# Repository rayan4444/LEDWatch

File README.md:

# LEDWatch
LEDWatch: documentation coming soon

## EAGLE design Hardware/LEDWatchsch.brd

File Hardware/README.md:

# LED Watch Hardware

<!-- Schematic and explanations  -->
<!-- PCB file and explanations -->
<!-- Assembly instructions -->
<!-- Ordering: BOM and PCB, maybe Tindie store? -->

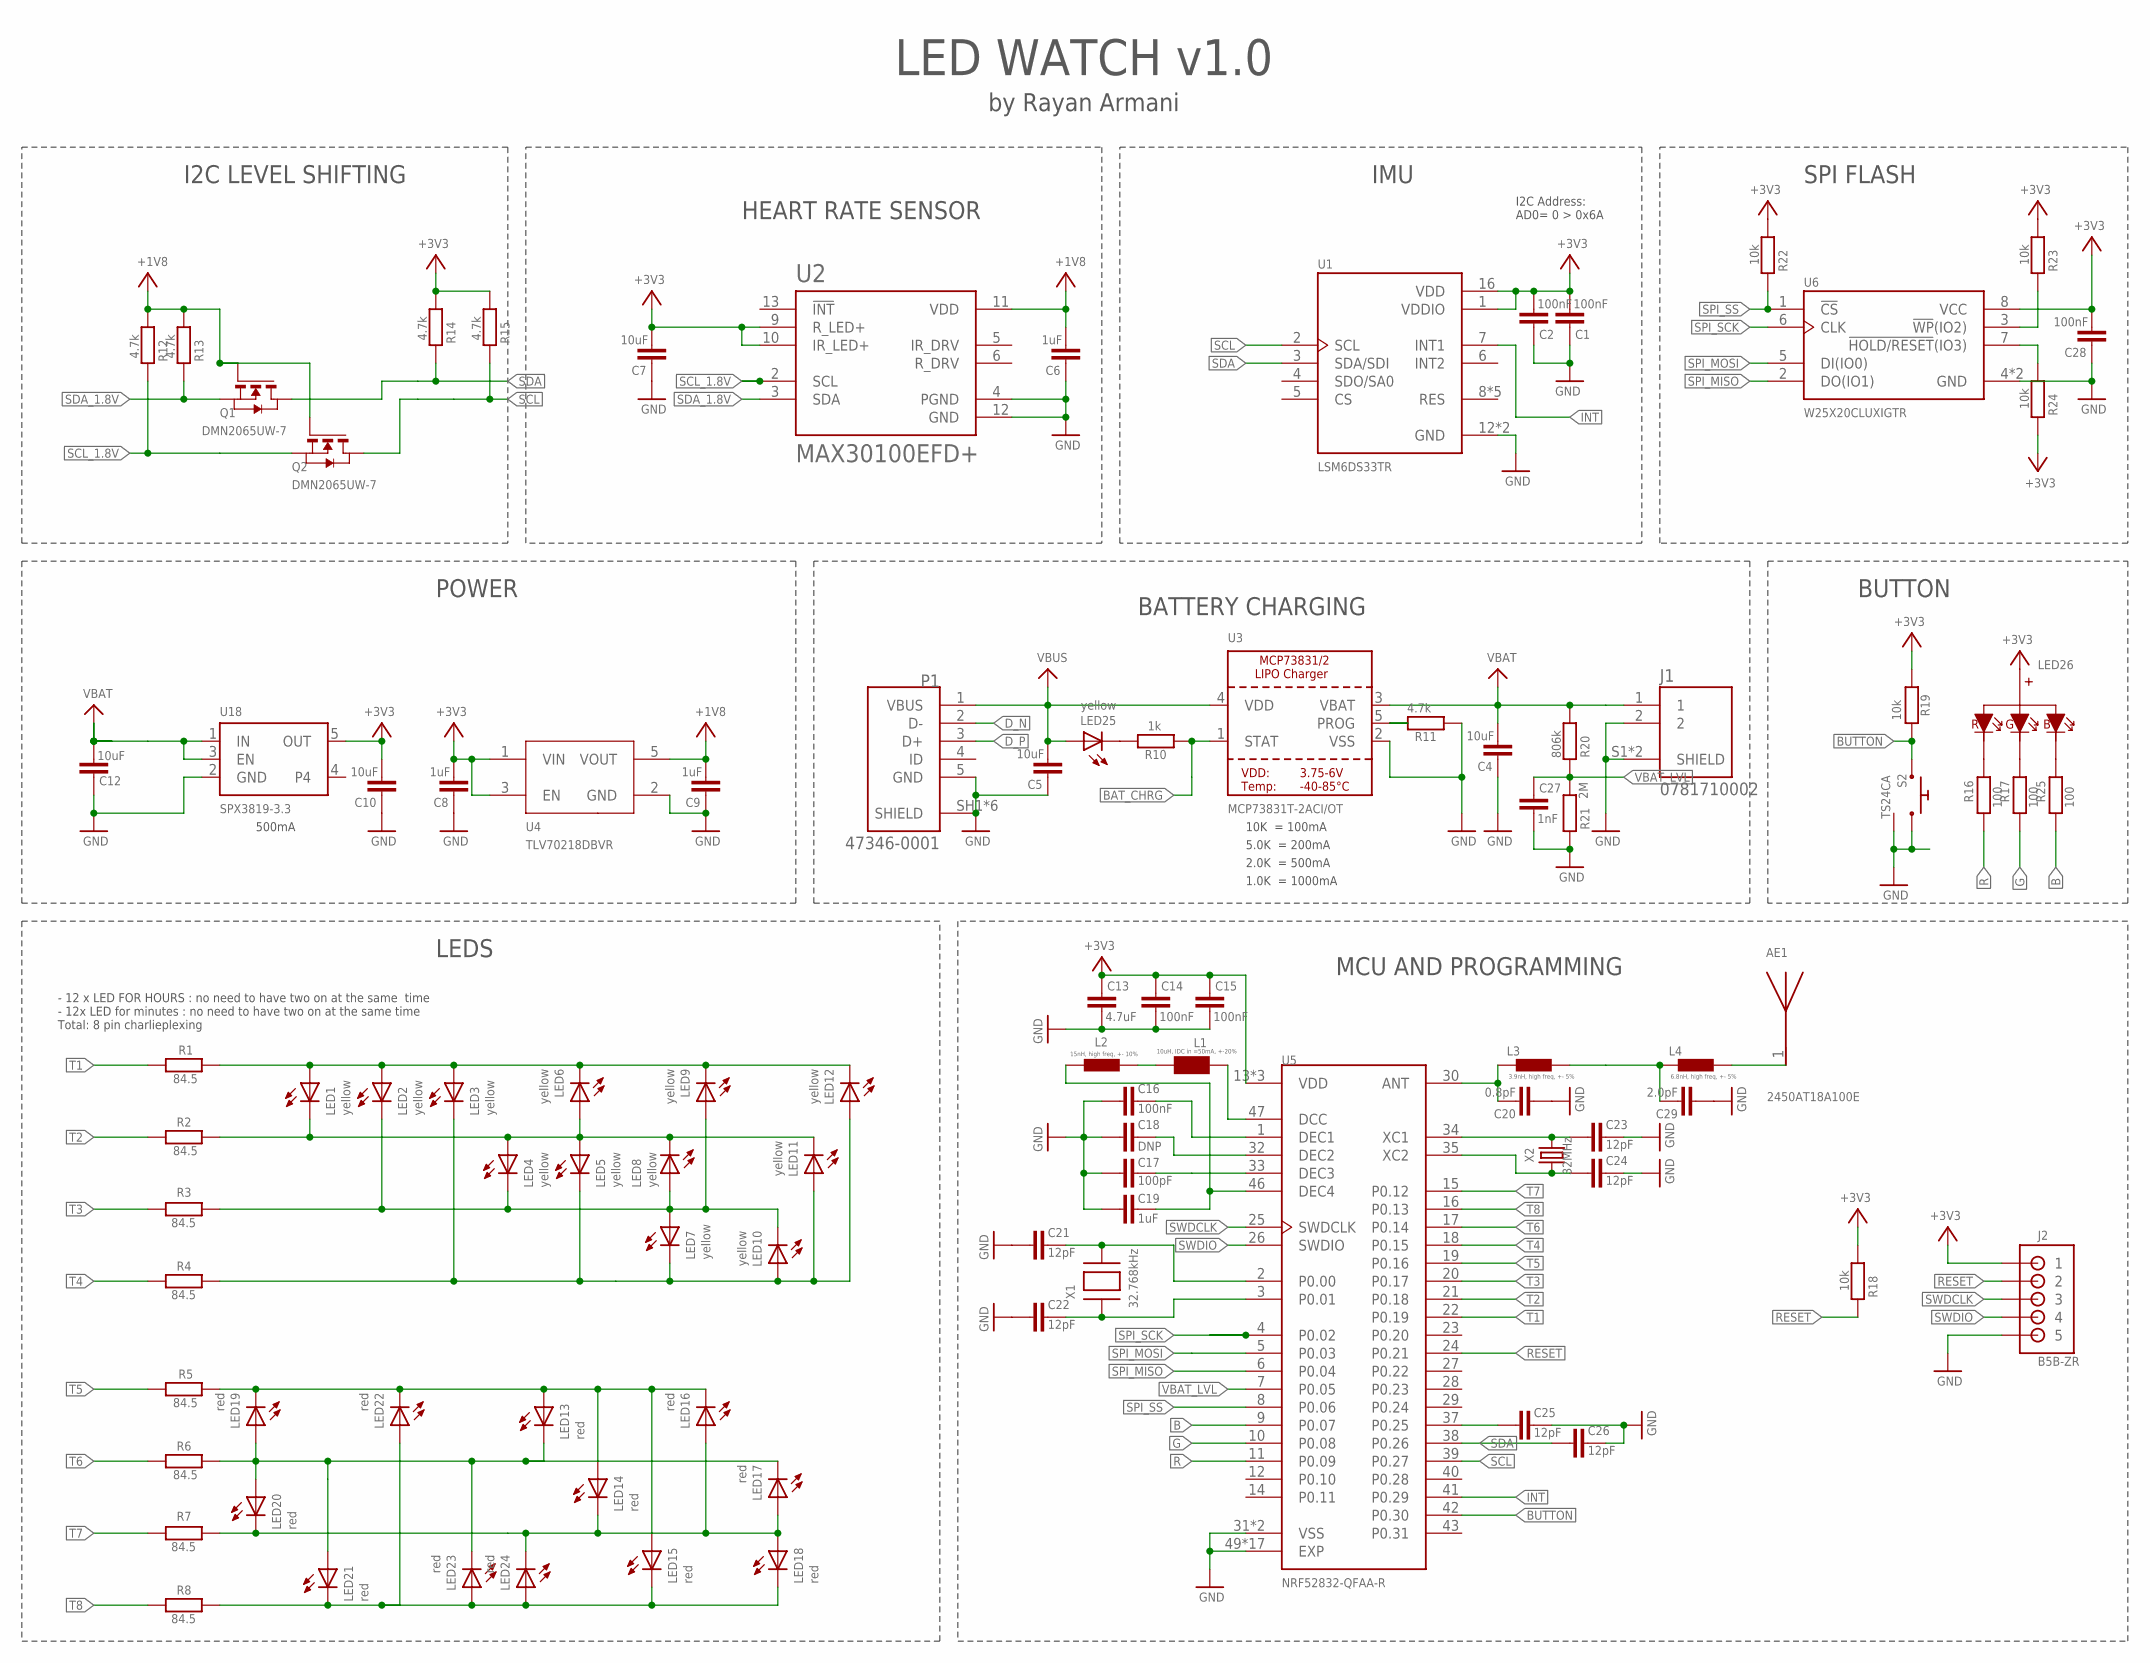
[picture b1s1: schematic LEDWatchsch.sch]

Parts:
AE1: 2450AT18A100E; ANTC3216X140N
C1, C2, C15, C28: 100nF; C0402K
C4, C5, C7, C10, C12: 10uF; C0402
C6, C8, C9: 1uF; C0402K
C13: 4.7uF; C0603
C14, C16: 100nF; C0402
C17: 100pF; C0402
C18: DNP; C0402
C19: 1uF; C0603
C20: 0.8pF; C0402
C21, C22, C23, C24, C25, C26: 12pF; C0402
C27: 1nF; C0402K
C29: 2.0pF; C0402
J1: 0781710002; MOLEX_0781710002
J2: B5B-ZR
L1: 10uH, IDC in =50mA, +-20%; WUERTH-ELEKTRONIK_0603
L2: 15nH, high freq, +- 10%; 0402
L3: 3.9nH, high freq, +- 5%; 0402
L4: 6.8nH, high freq, +- 5%; 0402
LED1, LED2, LED3, LED4, LED5, LED6, LED7, LED8, LED9, LED10, LED11, LED12, LED25: yellow; CHIPLED_0603
LED13, LED14, LED15, LED16, LED17, LED18, LED19, LED20, LED21, LED22, LED23, LED24: red; CHIPLED_0603
LED26: RGB_CAV1; 19-037A/RSGHBHW
P1: 47346-0001; MOLEX_47346-0001
Q1, Q2: DMN2065UW-7; SOT323
R1, R2, R3, R4, R5, R6, R7, R8: 84.5; R0402
R10: 1k; R0402
R11, R12, R13, R14, R15: 4.7k; R0402
R16, R17, R25: 100; R0402
R18, R19, R22, R23, R24: 10k; R0402
R20: 806k; R0402
R21: 2M; R0402
S2: TS24CA; TS24CCA_NOHOLE
U1: LSM6DS33TR; PQFN50P300X300X86-16N
U2: MAX30100EFD+; LGA14R80P2X7_560X280X130
U3: MCP73831T-2ACI/OT; SOT23-5
U4: TLV70218DBVR; SOT95P280X145-5N
U5: NRF52832-QFAA-R; QFN40P600X600X90-49N
U6: W25X20CLUXIGTR; SON50P300X200X60-9N
U18: SPX3819-3.3; SOT23-5
X1: 32.768kHz; XTAL3215
X2: 32MHz; 2.0X1.6_KX-5

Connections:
+3V3: C1.2, C2.2, C7.2, C8.2, C10.2, C13.1, C14.1, C15.1, C28.2, J2.1, LED26.A, R14.1, R15.1, R18.1, R19.1, R22.1, R23.1, R24.2, U1.1 (VDDIO), U1.16 (VDD), U2.9 (R_LED+), U2.10 (IR_LED+), U4.1 (VIN), U4.3 (EN), U5.13 (VDD), U5.36 (VDD), U5.48 (VDD), U6.8 (VCC), U18.5 (OUT)
ANT: C29.1, L3.2, L4.1
B: R25.1, U5.9 (P0.07)
BAT_CHRG: R10.1, U3.1 (STAT)
BUTTON: R19.2, S2.1, U5.42 (P0.30)
D_N: P1.2 (D-)
D_P: P1.3 (D+)
G: R17.1, U5.10 (P0.08)
GND: C1.1, C2.1, C4.1, C5.1, C6.1, C7.1, C8.1, C9.1, C10.1, C12.1, C13.2, C14.2, C15.2, C16.2, C17.2, C18.2, C19.1, C20.2, C21.2, C22.2, C23.1, C24.1, C25.1, C26.1, C27.2, C28.1, C29.2, J1.2, J1.S1 (SHIELD), J1.S2 (SHIELD), J2.5, P1.5 (GND), P1.SH1 (SHIELD), P1.SH2 (SHIELD), P1.SH3 (SHIELD), P1.SH4 (SHIELD), P1.SH5 (SHIELD), P1.SH6 (SHIELD), R11.1, R21.2, S2.2, S2.P$3 (SHIELD), S2.P$4 (SHIELD), U1.12 (GND), U1.13 (GND), U2.4 (PGND), U2.12 (GND), U3.2 (VSS), U4.2 (GND), U5.31 (VSS), U5.45 (VSS), U5.49 (EXP), U5.50 (EXP), U5.51 (EXP), U5.52 (EXP), U5.53 (EXP), U5.54 (EXP), U5.55 (EXP), U5.56 (EXP), U5.57 (EXP), U5.58 (EXP), U5.59 (EXP), U5.60 (EXP), U5.61 (EXP), U5.62 (EXP), U5.63 (EXP), U5.64 (EXP), U5.65 (EXP), U6.4 (GND), U6.9 (GND), U18.2 (GND)
H1: LED1.A, LED2.A, LED3.A, LED6.C, LED9.C, LED12.C, R1.2
H2: LED1.C, LED4.A, LED5.A, LED6.A, LED8.C, LED11.C, R2.2
H3: LED2.C, LED4.C, LED7.A, LED8.A, LED9.A, LED10.C, R3.2
H4: LED3.C, LED5.C, LED7.C, LED10.A, LED11.A, LED12.A, R4.2
H5: LED13.A, LED14.A, LED15.A, LED16.C, LED19.C, LED22.C, R5.2
H6: LED13.C, LED17.C, LED19.A, LED20.A, LED21.A, LED23.C, R6.2
H7: LED14.C, LED16.A, LED17.A, LED18.A, LED20.C, LED24.C, R7.2
H8: LED15.C, LED18.C, LED21.C, LED22.A, LED23.A, LED24.A, R8.2
INT: U1.7 (INT1), U5.41 (P0.29)
unnamed: LED25.C, R10.2
unnamed: C16.1, U5.1 (DEC1)
unnamed: R11.2, U3.5 (PROG)
unnamed: C18.1, U5.32 (DEC2)
unnamed: LED26.B, R25.2
unnamed: C17.1, U5.33 (DEC3)
unnamed: C19.2, L2.2, U5.46 (DEC4)
unnamed: L1.1, U5.47 (DCC)
unnamed: L1.2, L2.1
unnamed: C20.1, L3.1, U5.30 (ANT)
unnamed: C21.1, U5.2 (P0.00), X1.P$2
unnamed: C22.1, U5.3 (P0.01), X1.P$1
unnamed: C23.2, U5.34 (XC1), X2.3 (2)
unnamed: C24.2, U5.35 (XC2), X2.1
unnamed: C25.2, U5.37 (P0.25)
unnamed: R23.2, U6.3 (!WP!(IO2))
unnamed: R24.1, U6.7 (!HOLD/RESET!(IO3))
unnamed: AE1.1, L4.2
unnamed: LED26.R, R16.2
unnamed: LED26.G, R17.2
R: R16.1, U5.11 (P0.09)
RESET: J2.2, R18.2, U5.24 (P0.21)
SCL: Q2.3 (D), R15.2, U1.2 (SCL), U5.39 (P0.27)
SCL_1.8V: Q2.2 (S), R12.2, U2.2 (SCL)
SDA: C26.2, Q1.3 (D), R14.2, U1.3 (SDA/SDI), U5.38 (P0.26)
SDA_1.8V: Q1.2 (S), R13.2, U2.3 (SDA)
SPI_MISO: U5.6 (P0.04), U6.2 (DO(IO1))
SPI_MOSI: U5.5 (P0.03), U6.5 (DI(IO0))
SPI_SCK: U5.4 (P0.02), U6.6 (CLK)
SPI_SS: R22.2, U5.8 (P0.06), U6.1 (!CS)
SWDCLK: J2.3, U5.25 (SWDCLK)
SWDIO: J2.4, U5.26 (SWDIO)
T1: R1.1, U5.22 (P0.19)
T2: R2.1, U5.21 (P0.18)
T3: R3.1, U5.20 (P0.17)
T4: R4.1, U5.18 (P0.15)
T5: R5.1, U5.19 (P0.16)
T6: R6.1, U5.17 (P0.14)
T7: R7.1, U5.15 (P0.12)
T8: R8.1, U5.16 (P0.13)
VBAT: C4.2, C12.2, J1.1, R20.1, U3.3 (VBAT), U18.1 (IN), U18.3 (EN)
VBAT_LVL: C27.1, R20.2, R21.1, U5.7 (P0.05)
VBUS: C5.2, LED25.A, P1.1 (VBUS), U3.4 (VDD)
VCC: C6.2, C9.2, Q1.1 (G), Q2.1 (G), R12.1, R13.1, U2.11 (VDD), U4.5 (VOUT)

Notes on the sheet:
IMU
HEART RATE SENSOR
LED WATCH v1.0
BATTERY CHARGING
MCU AND PROGRAMMING
POWER
LEDS
- 12 x LED FOR HOURS : no need to have two on at the same time - 12x LED for minutes : no need to have two on at the same time Total: 8 pin charlieplexing
I2C Address: AD0= 0 > 0x6A
10K = 100mA
5.0K = 200mA
2.0K = 500mA
1.0K = 1000mA
500mA
I2C LEVEL SHIFTING
by Rayan Armani
BUTTON
SPI FLASH

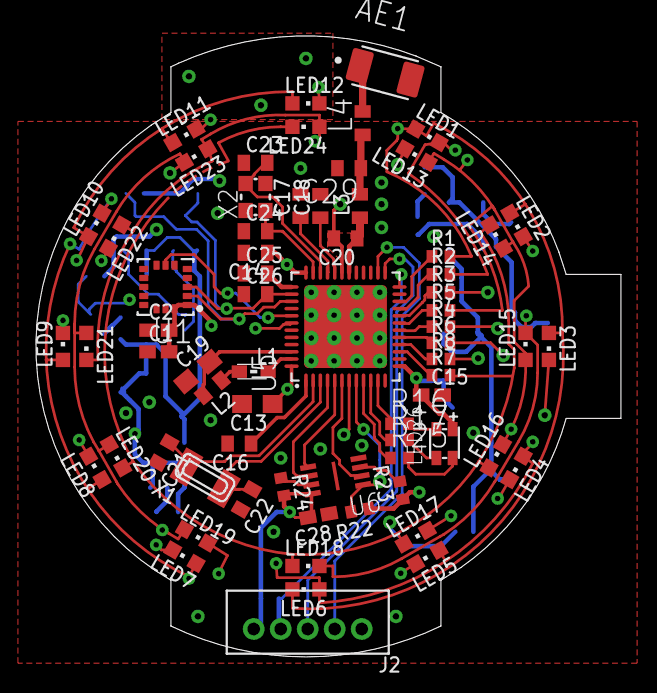
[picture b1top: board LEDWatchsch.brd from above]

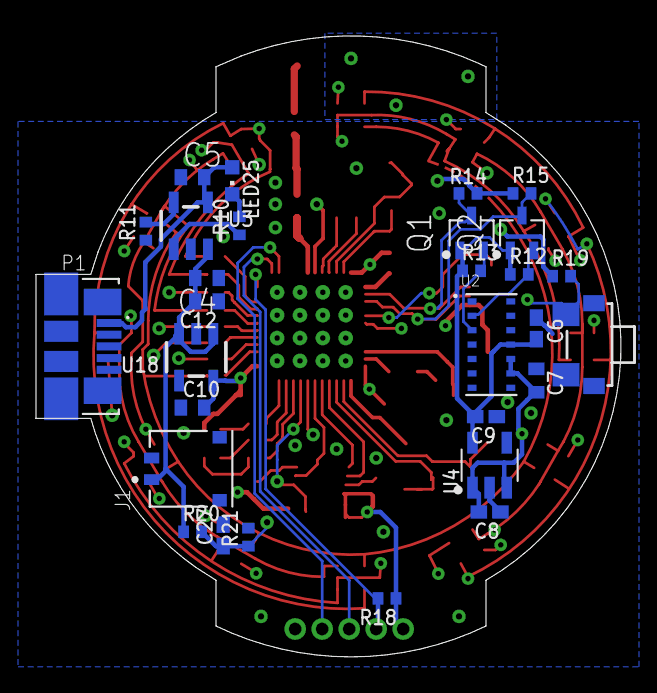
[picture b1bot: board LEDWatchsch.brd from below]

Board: 4 copper layers, 32.5 x 34.5 mm, 97 parts (29 on the bottom side), 60 nets.

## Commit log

2020-08-12 WIP update

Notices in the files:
parts and their libraries:
microbuilder: This work is placed in the public domain, and may be freely used for commercial and non-commercial work with the following conditions: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
crystal-geyer_V1_0: Copyright: Geyer-Electronic
